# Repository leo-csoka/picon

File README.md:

# picon
**picon** is an effort to emulate a Joy-Con using the original Raspberry Pi Pico W. This includes Bluetooth Classic HID support and a wired connection to the Switch. More information will be available soon.

## repository structure
```text
.
├── .gitignore
├── build.sh
├── CMakeLists.txt
├── LICENSE
├── pico_sdk_import.cmake
├── push.sh
├── README.md
├── src/
│   ├── btstack_config.h
│   ├── btstack_config_common.h
│   ├── joycon.c
│   ├── joycon.h
│   ├── joycon_bt.c
│   ├── joycon_bt.h
│   ├── joycon_descriptor.c
│   ├── joycon_descriptor.h
│   └── main.c
├── kicad/
│   ├── module/
│   │   └── kicad project files
│   └── smd-board/
│       └── kicad project files
├── tests/
│   └── keyboard_demo.py
└── TODO.txt
```

**last updated**: Oct 22, 2026

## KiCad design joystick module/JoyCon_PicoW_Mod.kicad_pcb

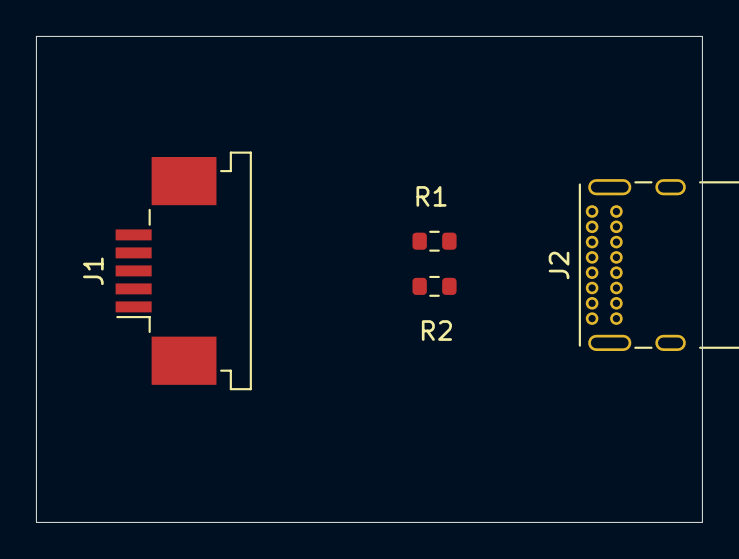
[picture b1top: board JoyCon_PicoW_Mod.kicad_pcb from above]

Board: 2 copper layers, 37.0 x 27.0 mm, 4 parts (0 on the bottom side), 4 nets, no tracks yet.

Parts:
J1: Conn_01x05_Socket; TE_84953-5_1x05-1MP_P1.0mm_Horizontal
J2: USB_C_Receptacle_USB2.0_16P; USB_C_Receptacle_GCT_USB4085
R1, R2: 5.1k ohms; R_0603_1608Metric

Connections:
GND: J1.4, J1.5, J2.A1 (GND), J2.A5 (CC1), J2.A7 (D-), J2.A12 (GND), J2.B1 (GND), J2.B5 (CC2), J2.B7 (D-), J2.B12 (GND), J2.SH (SHIELD), R1.1, R1.2, R2.1, R2.2
unnamed: J1.1, J2.A4 (VBUS), J2.A9 (VBUS), J2.B4 (VBUS), J2.B9 (VBUS)
unnamed: J1.2, J2.A6 (D+), J2.B6 (D+)
unnamed: J1.3, J2.A8 (SBU1)
